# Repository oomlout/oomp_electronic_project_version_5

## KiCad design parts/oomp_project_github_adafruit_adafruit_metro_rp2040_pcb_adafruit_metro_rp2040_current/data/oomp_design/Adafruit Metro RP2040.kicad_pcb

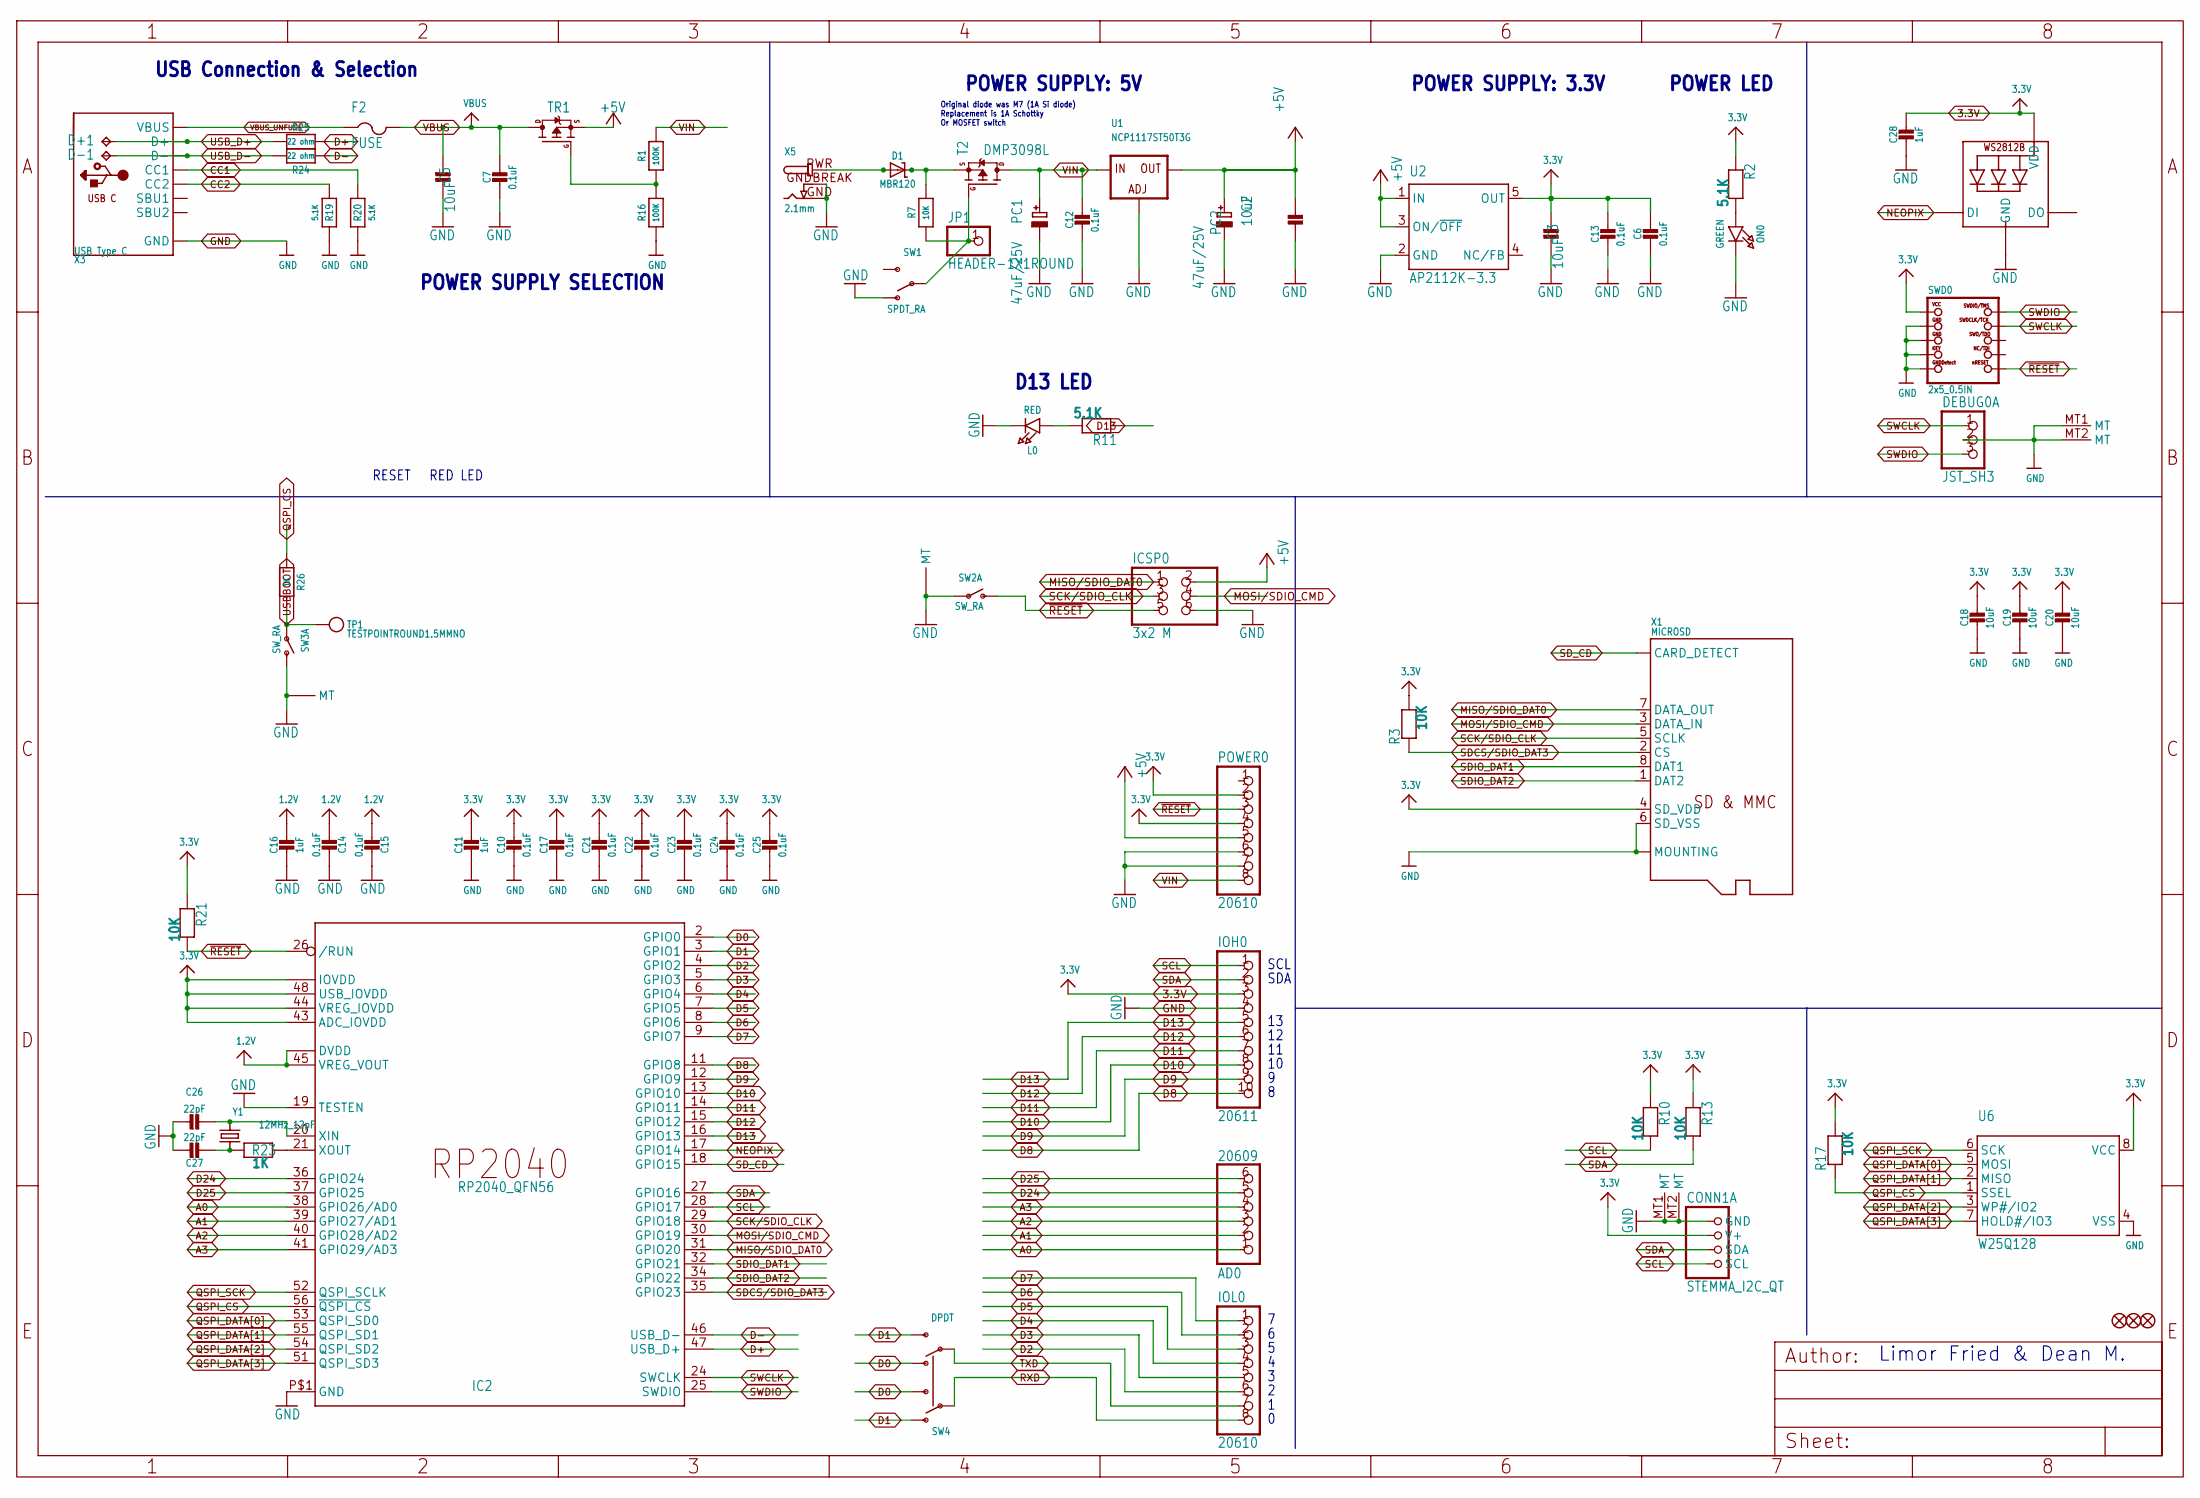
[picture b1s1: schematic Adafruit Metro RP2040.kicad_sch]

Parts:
AD0: 20609; 1X06_OVALWAVE
C2, C3, C5, C18, C19, C20: 10uF; 0805-NO
C6, C7, C10, C12, C13, C14, C15, C17, C21, C22, C23, C24, C25: 0.1uF; 0603-NO
C11, C16, C28: 1uF; 0603-NO
C26, C27: 22pF; 0603-NO
CONN1: STEMMA_I2C_QT; JST_SH4; LCSC C2845363
D1: MBR120; SOD-123
D+1: TPB1,27; B1,27
D-1: TPB1,27; B1,27
DEBUG0: JST_SH3
F2: FUSE; R1206
FD1, FD2, FD3: FIDUCIAL_1MM
IC2: RP2040_QFN56; QFN56_7MM_REDUCEDEPAD; LCSC C2040
ICSP0: 3x2 M; 2X03_ROUND_70MIL
IOH0: 20611; 1X10_OVALWAVE
IOL0: 20610; 1X08_OVALWAVE
JP1: HEADER-1X1ROUND; 1X01_ROUND
L0: RED; CHIPLED_0603_NOOUTLINE
LED2: WS2812B_3535FULL; LED3535_FULLPADS
ON0: GREEN; CHIPLED_0603_NOOUTLINE
PC1, PC2: 47uF/25V; PANASONIC_D
POWER0: 20610; 1X08_OVALWAVE
R1, R16: 100K; 0603-NO
R2, R11, R19, R20: 5.1K; 0603-NO
R3, R7, R10, R13, R17, R21: 10K; 0603-NO
R23, R26: 1K; 0603-NO
R24, R25: 22 ohm; 0603-NO
SW1: SPDT_RA; SPDT_SMT_SSSS811101
SW2, SW3: SW_RA; SPST_TACTILE_RA; LCSC C778159
SW4: DPDT; EG1390; LCSC C2837066
SWD0: 2x5_0.5IN; 2X05_1.27MM_BOX_POSTS
T2: DMP3098L; SOT23-WIDE
TP1: TESTPOINTROUND1.5MMNO; TESTPOINT_ROUND_1.5MM_NO
TR1: DMP3098L; SOT23-WIDE
U1: NCP1117ST50T3G; SOT223-R
U2: AP2112K-3.3; SOT23-DBV
U6: W25Q128; SOIC8_208MIL
X1: MICROSD; JLC_ROTATION 90
X3: USB Type C; USB_C_CUSB31-CFM2AX-01-X; LCSC C165948
X5: 2.1mm; DCJACK_2MM_PTH
Y1: 12MHz_12pF; CRYSTAL_2.5X2

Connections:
1.2V: C14.2, C15.2, C16.1, IC2.23 (DVDD), IC2.45 (VREG_VOUT), IC2.50 (DVDD)
3.3V: C3.2, C6.2, C10.1, C11.1, C13.1, C17.1, C18.1, C19.1, C20.1, C21.1, C22.1, C23.1, C24.1, C25.1, C28.1, CONN1.2 (V+), IC2.1 (IOVDD), IC2.10 (IOVDD), IC2.22 (IOVDD), IC2.33 (IOVDD), IC2.42 (IOVDD), IC2.43 (ADC_IOVDD), IC2.44 (VREG_IOVDD), IC2.48 (USB_IOVDD), IC2.49 (IOVDD), IOH0.3, LED2.2 (VDD), POWER0.2, POWER0.4, R2.1, R3.2, R10.1, R13.1, R17.2, R21.1, SWD0.1 (VCC), U2.5 (OUT), U6.8 (VCC), X1.4 (SD_VDD)
+5V: C2.2, ICSP0.2, PC2.+, POWER0.5, TR1.2 (S), U1.2 (OUT), U1.4 (OUT), U2.1 (IN), U2.3 (ON/~OFF)
A0: AD0.1, IC2.38 (GPIO26/AD0)
A1: AD0.2, IC2.39 (GPIO27/AD1)
A2: AD0.3, IC2.40 (GPIO28/AD2)
A3: AD0.4, IC2.41 (GPIO29/AD3)
CC1: R20.2, X3.A5 (CC1)
CC2: R19.2, X3.B5 (CC2)
D0: IC2.2 (GPIO0), SW4.O2, SW4.S1
D1: IC2.3 (GPIO1), SW4.O1, SW4.S2
D2: IC2.4 (GPIO2), IOL0.6
D3: IC2.5 (GPIO3), IOL0.5
D4: IC2.6 (GPIO4), IOL0.4
D5: IC2.7 (GPIO5), IOL0.3
D6: IC2.8 (GPIO6), IOL0.2
D7: IC2.9 (GPIO7), IOL0.1
D8: IC2.11 (GPIO8), IOH0.10
D9: IC2.12 (GPIO9), IOH0.9
D10: IC2.13 (GPIO10), IOH0.8
D11: IC2.14 (GPIO11), IOH0.7
D12: IC2.15 (GPIO12), IOH0.6
D13: IC2.16 (GPIO13), IOH0.5, R11.1
D24: AD0.5, IC2.36 (GPIO24)
D25: AD0.6, IC2.37 (GPIO25)
D+: IC2.47 (USB_D+), R25.2
D-: IC2.46 (USB_D-), R24.2
GND: C2.1, C3.1, C5.1, C6.1, C7.2, C10.2, C11.2, C12.2, C13.2, C14.1, C15.1, C16.2, C17.2, C18.2, C19.2, C20.2, C21.2, C22.2, C23.2, C24.2, C25.2, C26.1, C27.1, C28.2, CONN1.1 (GND), CONN1.MT1 (MT), CONN1.MT2 (MT), DEBUG0.2, DEBUG0.MT1 (MT), DEBUG0.MT2 (MT), IC2.19 (TESTEN), IC2.P$1 (GND), ICSP0.6, IOH0.4, L0.C, LED2.4 (GND), ON0.C, PC1.-, PC2.-, POWER0.6, POWER0.7, R16.1, R19.1, R20.1, SW1.A (O), SW2.1, SW2.MT1 (MT), SW2.MT2 (MT), SW3.2 (S), SW3.MT1 (MT), SW3.MT2 (MT), SWD0.3 (GND), SWD0.5 (GND), SWD0.7 (KEY), SWD0.9 (GNDDETECT), U1.1 (ADJ), U2.2 (GND), U6.4 (VSS), X1.6 (SD_VSS), X1.MT1 (MOUNTING), X1.MT2 (MOUNTING), X3.A1B12 (GND), X3.B1A12 (GND), X5.GND, X5.GNDBREAK
MISO/SDIO_DAT0: IC2.31 (GPIO20), ICSP0.1, X1.7 (DATA_OUT)
MOSI/SDIO_CMD: IC2.30 (GPIO19), ICSP0.4, X1.3 (DATA_IN)
unnamed: L0.A, R11.2
unnamed: ON0.A, R2.2
unnamed: C26.2, IC2.20 (XIN), Y1.3 (2)
unnamed: C27.2, R23.1, Y1.1
unnamed: R1.1, R16.2, TR1.1 (G)
unnamed: IC2.21 (XOUT), R23.2
unnamed: D1.C, R7.2, T2.2 (S)
NEOPIX: IC2.17 (GPIO14), LED2.1 (DI)
PWRIN: D1.A, X5.PWR
PWR_SWITCH: JP1.1, R7.1, SW1.B, T2.1 (G)
QSPI_CS: IC2.56 (~QSPI_CS), R17.1, R26.1, U6.1 (SSEL)
QSPI_DATA[0]: IC2.53 (QSPI_SD0), U6.5 (MOSI)
QSPI_DATA[1]: IC2.55 (QSPI_SD1), U6.2 (MISO)
QSPI_DATA[2]: IC2.54 (QSPI_SD2), U6.3 (WP#/IO2)
QSPI_DATA[3]: IC2.51 (QSPI_SD3), U6.7 (HOLD#/IO3)
QSPI_SCK: IC2.52 (QSPI_SCLK), U6.6 (SCK)
RXD: IOL0.8, SW4.P1
SCK/SDIO_CLK: IC2.29 (GPIO18), ICSP0.3, X1.5 (SCLK)
SCL: CONN1.4 (SCL), IC2.28 (GPIO17), IOH0.1, R10.2
SDA: CONN1.3 (SDA), IC2.27 (GPIO16), IOH0.2, R13.2
SDCS/SDIO_DAT3: IC2.35 (GPIO23), R3.1, X1.2 (CS)
SDIO_DAT1: IC2.32 (GPIO21), X1.8 (DAT1)
SDIO_DAT2: IC2.34 (GPIO22), X1.1 (DAT2)
SD_CD: IC2.18 (GPIO15), X1.CD1 (CARD_DETECT), X1.CD2 (CARD_DETECT)
SWCLK: DEBUG0.1, IC2.24 (SWCLK), SWD0.4 (SWDCLK)
SWDIO: DEBUG0.3, IC2.25 (SWDIO), SWD0.2 (SWDIO)
TXD: IOL0.7, SW4.P2
USBBOOT: R26.2, SW3.1, TP1.P$1
USB_D+: D+1.TP, R25.1, X3.A6 (D+), X3.B6 (D+)
USB_D-: D-1.TP, R24.1, X3.A7 (D-), X3.B7 (D-)
VBUS: C5.2, C7.1, F2.2, TR1.3 (D)
VBUS_UNFUSE: F2.1, X3.A4B9 (VBUS), X3.B4A9 (VBUS)
VIN: C12.1, PC1.+, POWER0.8, R1.2, T2.3 (D), U1.3 (IN)
~RESET: IC2.26 (/RUN), ICSP0.5, POWER0.3, R21.2, SW2.2 (S), SWD0.10 (NRESET)

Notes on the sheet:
D13 LED
RESET
SCL
SDA
POWER LED
POWER SUPPLY: 5V
Limor Fried & Dean M.
POWER SUPPLY: 3.3V
POWER SUPPLY SELECTION
USB Connection & Selection
RED LED
Original diode was M7 (1A Si diode) Replacement is 1A Schottky Or MOSFET switch

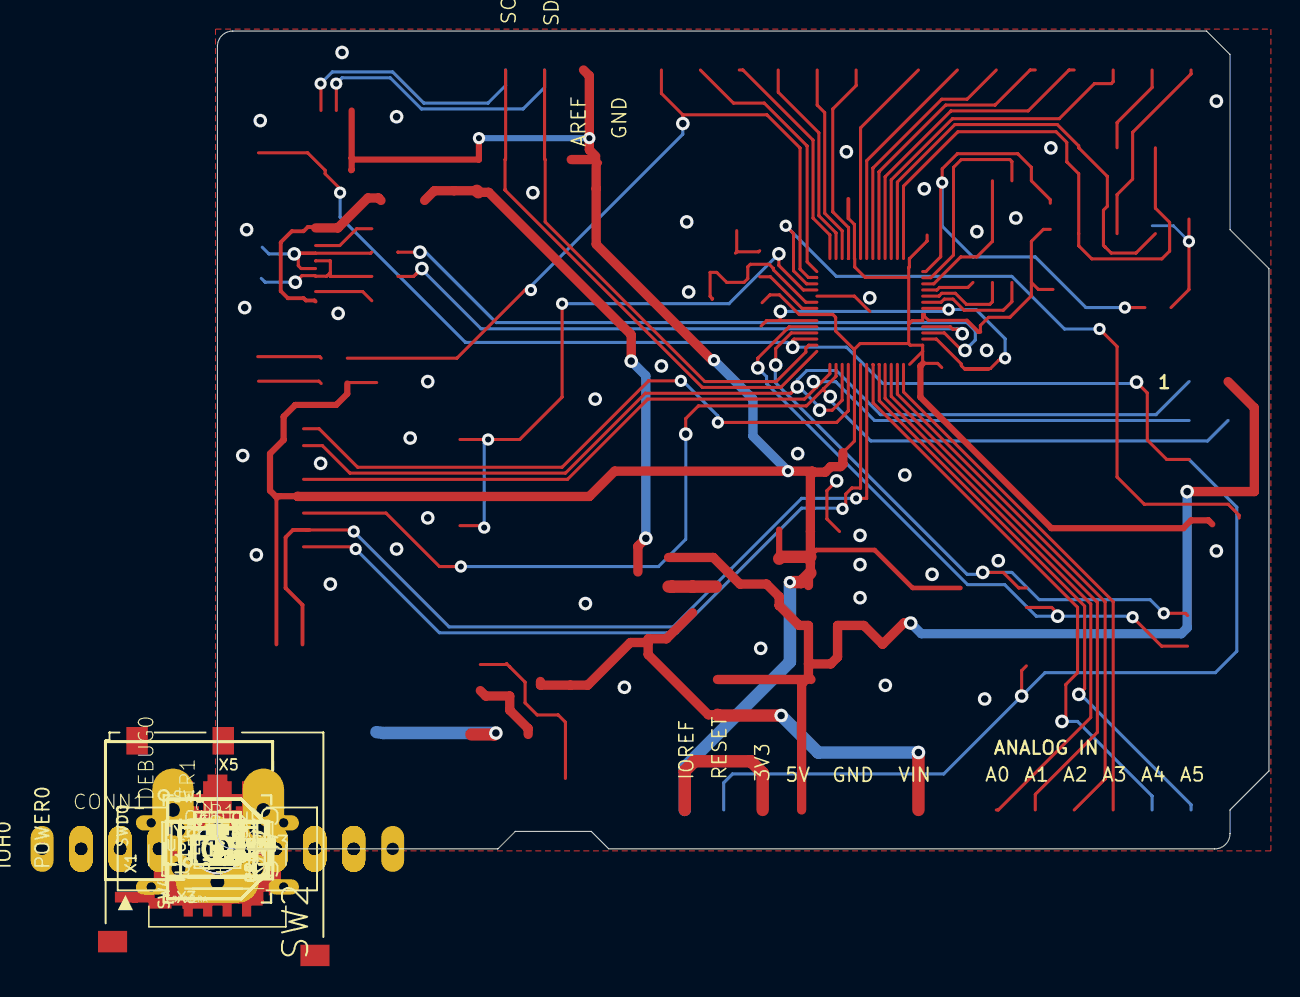
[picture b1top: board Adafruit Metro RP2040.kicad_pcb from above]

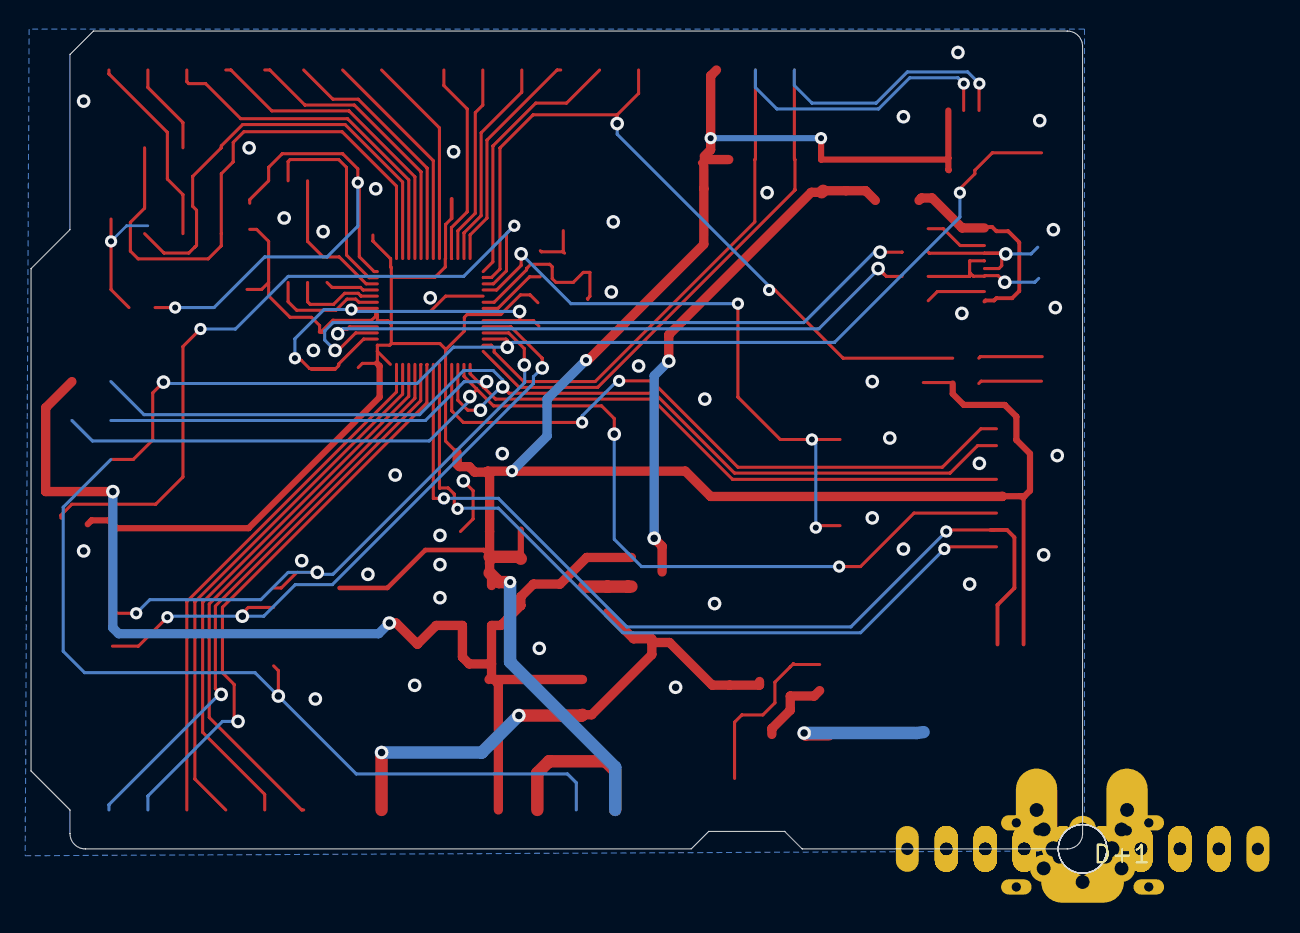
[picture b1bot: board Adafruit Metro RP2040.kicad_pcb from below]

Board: 2 copper layers, 68.6 x 53.3 mm, 83 parts (4 on the bottom side), 64 nets.

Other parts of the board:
U$11: PCBFEAT-REV-040
U$15: METRO_RP2040_BOT
U$29: METRO_RP2040_TOP
UNK_HOLE_0: dummyfp0
UNK_HOLE_1: dummyfp1
UNK_HOLE_2: dummyfp2
UNK_HOLE_3: dummyfp3

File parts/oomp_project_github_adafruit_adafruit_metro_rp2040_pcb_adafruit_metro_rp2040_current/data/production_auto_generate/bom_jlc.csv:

Comment,Designator,Footprint,LCSC Part #
,JP1,Adafruit Metro RP2040-import-fps:1X01_ROUND,C7501259
,U$15,Adafruit Metro RP2040-import-fps:METRO_RP2040_BOT,
,U$29,Adafruit Metro RP2040-import-fps:METRO_RP2040_TOP,
,U$11,Adafruit Metro RP2040-import-fps:PCBFEAT-REV-040,
,TP1,Adafruit Metro RP2040-import-fps:TESTPOINT_ROUND_1.5MM_NO,
0.1uF,"C6,C7,C10,C12,C13,C14,C15,C17,C21,C22,C23,C24,C25",Adafruit Metro RP2040-import-fps:0603-NO,C14663
100K,"R1,R16",Adafruit Metro RP2040-import-fps:0603-NO,C25803
10K,"R3,R7,R10,R13,R17,R21",Adafruit Metro RP2040-import-fps:0603-NO,C98220
10uF,"C2,C3,C5,C18,C19,C20",Adafruit Metro RP2040-import-fps:0805-NO,
12MHz_12pF,Y1,Adafruit Metro RP2040-import-fps:CRYSTAL_2.5X2,
1K,"R23,R26",Adafruit Metro RP2040-import-fps:0603-NO,C2907002
1uF,"C11,C16,C28",Adafruit Metro RP2040-import-fps:0603-NO,C5673
2.1mm,X5,Adafruit Metro RP2040-import-fps:DCJACK_2MM_PTH,
20609,AD0,Adafruit Metro RP2040-import-fps:1X06_OVALWAVE,C37208
20610,"IOL0,POWER0",Adafruit Metro RP2040-import-fps:1X08_OVALWAVE,C492421
20611,IOH0,Adafruit Metro RP2040-import-fps:1X10_OVALWAVE,C57369
22 ohm,"R24,R25",Adafruit Metro RP2040-import-fps:0603-NO,C23345
22pF,"C26,C27",Adafruit Metro RP2040-import-fps:0603-NO,C105620
2x5_0.5IN,SWD0,Adafruit Metro RP2040-import-fps:2X05_1.27MM_BOX_POSTS,
3x2 M,ICSP0,Adafruit Metro RP2040-import-fps:2X03_ROUND_70MIL,
47uF/25V,"PC1,PC2",Adafruit Metro RP2040-import-fps:PANASONIC_D,
5.1K,"R2,R11,R19,R20",Adafruit Metro RP2040-import-fps:0603-NO,C23186
AP2112K-3.3,U2,Adafruit Metro RP2040-import-fps:SOT23-DBV,
DMP3098L,"T2,TR1",Adafruit Metro RP2040-import-fps:SOT23-WIDE,
DPDT,SW4,Adafruit Metro RP2040-import-fps:EG1390,
FIDUCIAL_1MM,"FD1,FD2,FD3",Adafruit Metro RP2040-import-fps:FIDUCIAL_1MM,
FUSE,F2,Adafruit Metro RP2040-import-fps:R1206,
GREEN,ON0,Adafruit Metro RP2040-import-fps:CHIPLED_0603_NOOUTLINE,
JST_SH3,DEBUG0,Adafruit Metro RP2040-import-fps:JST_SH3,
MBR120,D1,Adafruit Metro RP2040-import-fps:SOD-123,
MICROSD,X1,Adafruit Metro RP2040-import-fps:MICROSD,
NCP1117ST50T3G,U1,Adafruit Metro RP2040-import-fps:SOT223-R,
RED,L0,Adafruit Metro RP2040-import-fps:CHIPLED_0603_NOOUTLINE,
RP2040_QFN56,IC2,Adafruit Metro RP2040-import-fps:QFN56_7MM_REDUCEDEPAD,
SPDT_RA,SW1,Adafruit Metro RP2040-import-fps:SPDT_SMT_SSSS811101,
STEMMA_I2C_QT,CONN1,Adafruit Metro RP2040-import-fps:JST_SH4,C160404
SW_RA,"SW2,SW3",Adafruit Metro RP2040-import-fps:SPST_TACTILE_RA,
"TPB1,27","D+1,D-1","Adafruit Metro RP2040-import-fps:B1,27",
USB Type C,X3,Adafruit Metro RP2040-import-fps:USB_C_CUSB31-CFM2AX-01-X,
W25Q128,U6,Adafruit Metro RP2040-import-fps:SOIC8_208MIL,
WS2812B_3535FULL,LED2,Adafruit Metro RP2040-import-fps:LED3535_FULLPADS,

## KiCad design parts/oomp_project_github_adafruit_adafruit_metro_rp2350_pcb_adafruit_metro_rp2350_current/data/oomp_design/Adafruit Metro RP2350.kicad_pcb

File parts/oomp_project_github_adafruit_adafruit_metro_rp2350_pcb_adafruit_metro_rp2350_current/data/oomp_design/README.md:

# OOMP KiCad design copy

Open `Adafruit Metro RP2350.kicad_pro` (or the `.kicad_pcb` / `.kicad_sch`) in KiCad. Local OOMP libraries are under `libraries/`. Original inputs are preserved in [../original/](../original/).

Only verified unchanged installed KiCad defaults were renamed. Modified, custom, unmatched and unavailable items remain unchanged. Soldering variants are never swapped during conversion. Existing pad coordinates, nets and UUIDs are preserved.

See [conversion_report.yaml](conversion_report.yaml) for every conversion and skip. Copy this directory before editing; regeneration refuses to overwrite edited design files.

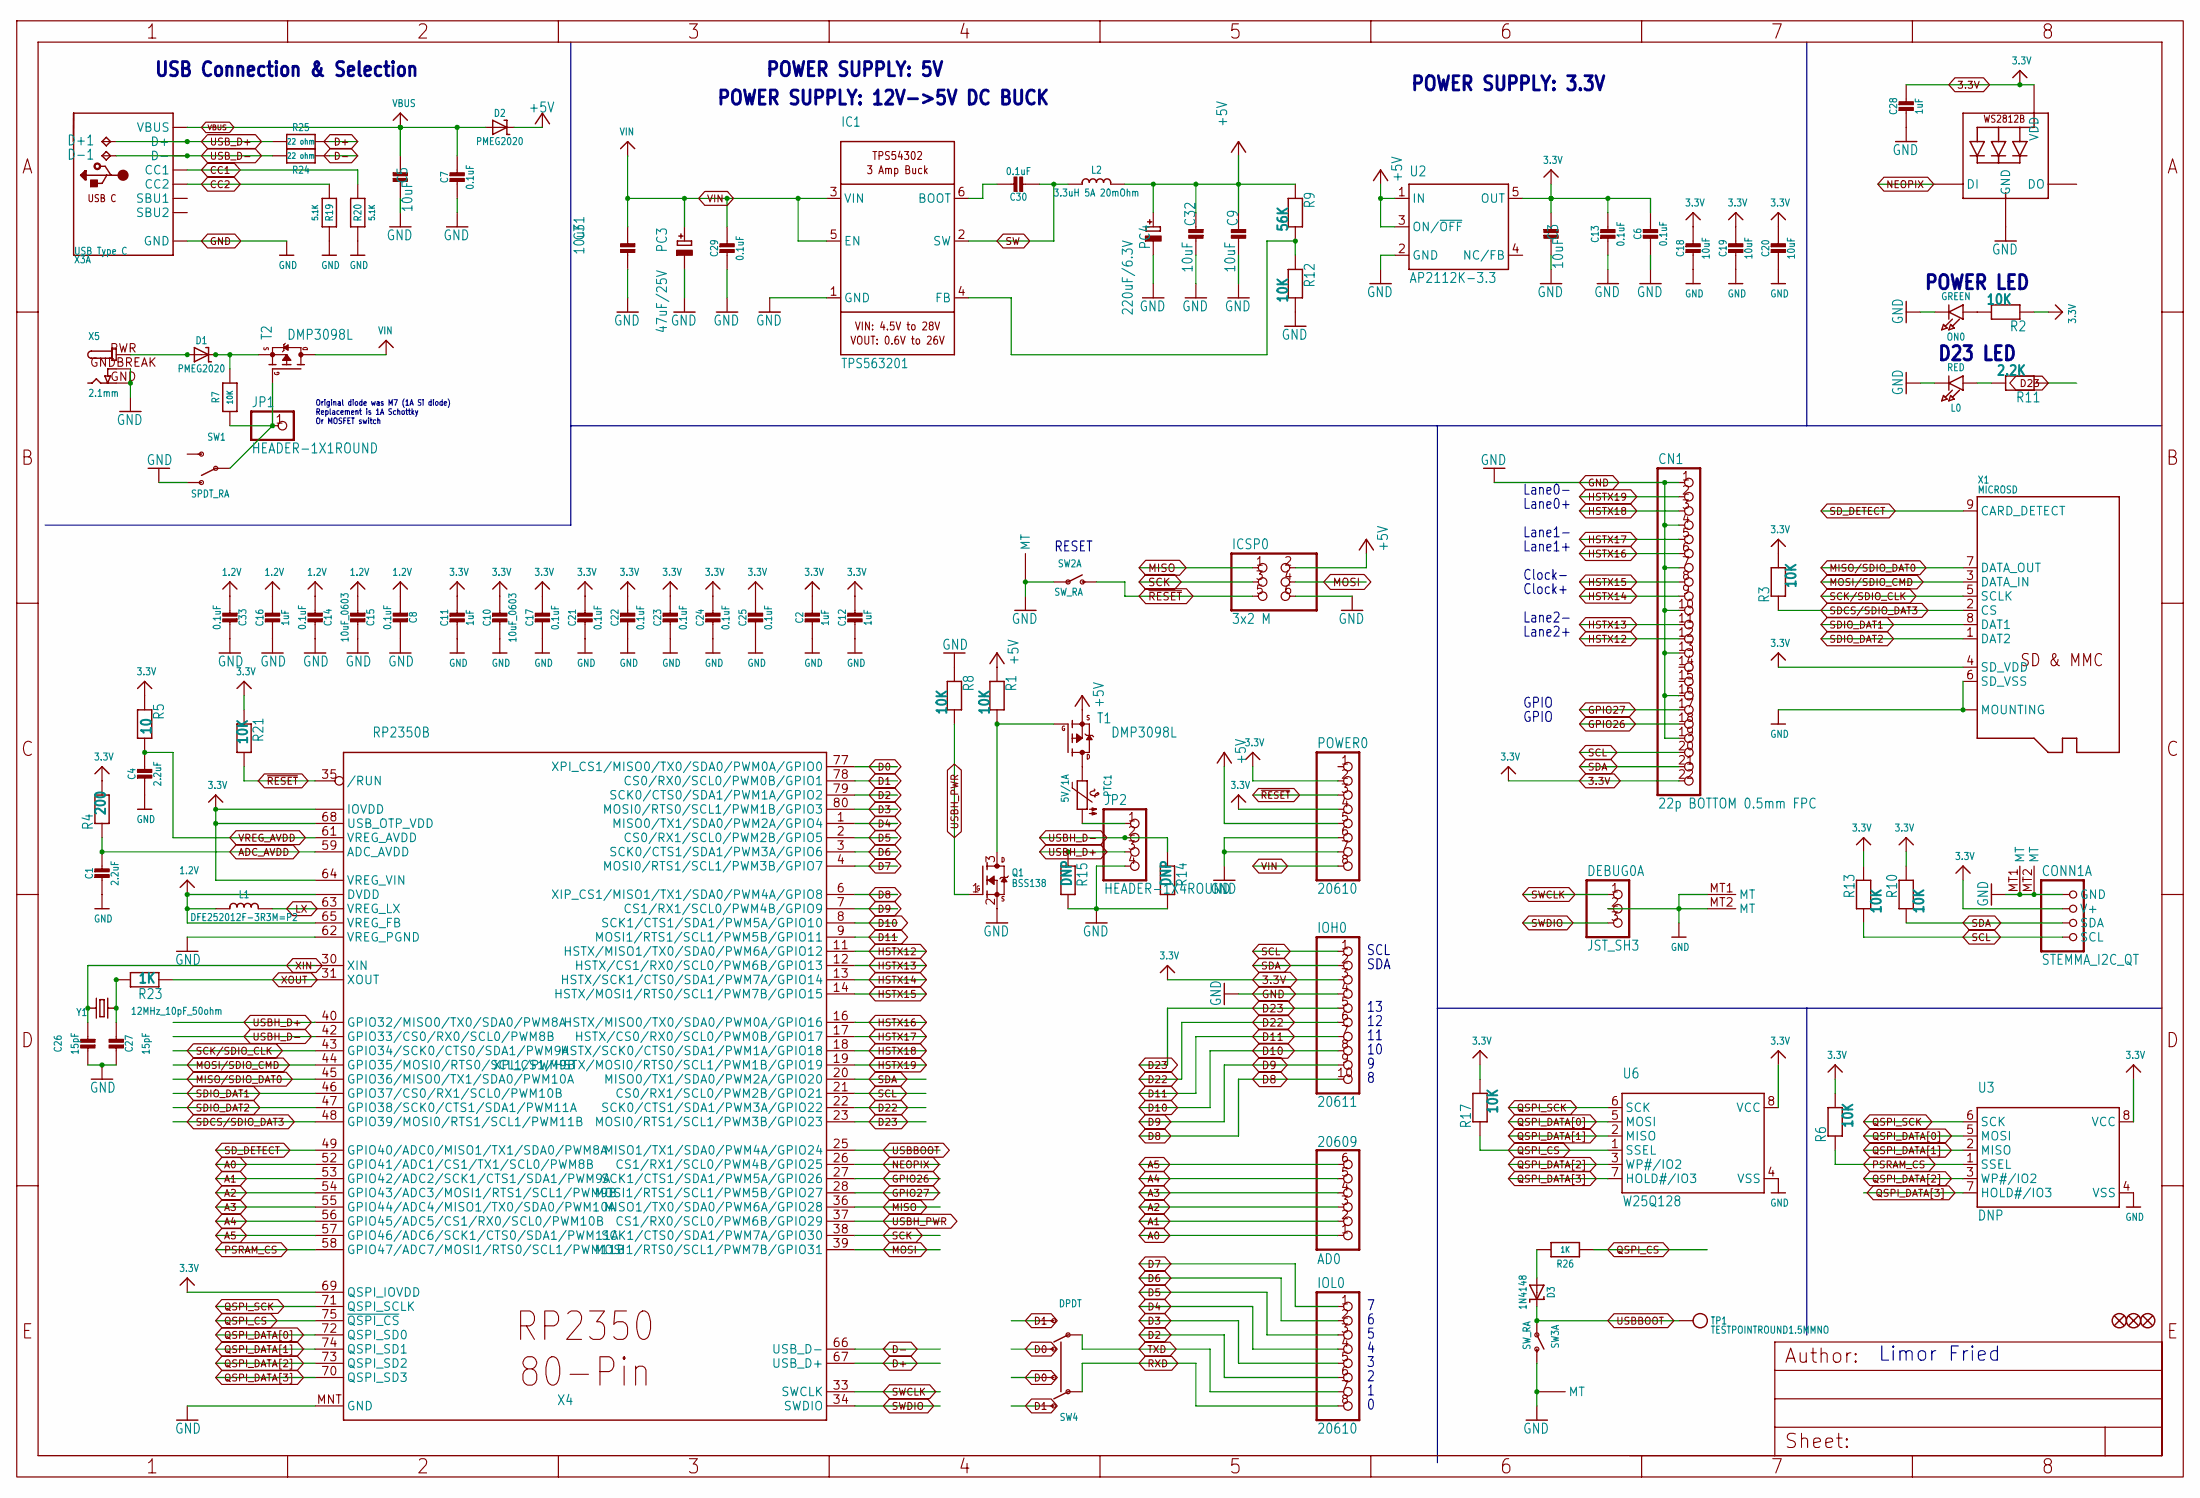
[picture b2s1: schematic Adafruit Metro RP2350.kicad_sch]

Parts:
AD0: 20609; 1X06_OVALWAVE
C1, C4: 2.2uF; 0603-NO
C2, C11, C12, C16, C28: 1uF; 0603-NO
C3, C5, C9, C18, C19, C20, C31, C32: 10uF; 0805-NO
C6, C7, C8, C13, C14, C17, C21, C22, C23, C24, C25, C29, C30, C33: 0.1uF; 0603-NO
C10, C15: 10uF_0603; 0603-NO_WIDE
C26, C27: 15pF; 0603-NO
CN1: 22p BOTTOM 0.5mm FPC; FPC_22PIN
CONN1: STEMMA_I2C_QT; JST_SH4; LCSC C2845363
D1, D2: PMEG2020; SOD-323
D3: 1N4148; SOD-323
D+1: TPB1,27; B1,27
D-1: TPB1,27; B1,27
DEBUG0: JST_SH3; JST_SH3_RA
FD1, FD2, FD3: FIDUCIAL_1MM
IC1: TPS563201; SOT23-6
ICSP0: 3x2 M; 2X03_ROUND_70MIL
IOH0: 20611; 1X10_OVALWAVE
IOL0: 20610; 1X08_OVALWAVE
JP1: HEADER-1X1ROUND; 1X01_ROUND
JP2: HEADER-1X4ROUND; 1X04_ROUND
L0: RED; CHIPLED_0603_NOOUTLINE
L1: DFE252012F-3R3M=P2; INDUCTOR_1007
L2: 3.3uH 5A 20mOhm; INDUCTOR_0603S
LED2: WS2812B_3535FULL; LED3535_FULLPADS
ON0: GREEN; CHIPLED_0603_NOOUTLINE
PC3: 47uF/25V; PANASONIC_D
PC4: 220uF/6.3V; PANASONIC_D
POWER0: 20610; 1X08_OVALWAVE
PTC1: 5V/1A; 0805-NO
Q1: BSS138; SOT23-WIDE
R1, R2, R3, R6, R7, R8, R10, R12, R13, R17, R21: 10K; 0603-NO
R4: 200; 0603-NO
R5: 10; 0603-NO
R9: 56K; 0603-NO
R11: 2.2K; 0603-NO
R14, R15: DNP; 0603-NO
R19, R20: 5.1K; 0603-NO
R23, R26: 1K; 0603-NO
R24, R25: 22 ohm; 0603-NO
SW1: SPDT_RA; SPDT_SMT_SSSS811101
SW2, SW3: SW_RA; SPST_TACTILE_RA; LCSC C778159
SW4: DPDT; EG1390; LCSC C2837066
T1, T2: DMP3098L; SOT23-WIDE
TP1: TESTPOINTROUND1.5MMNO; TESTPOINT_ROUND_1.5MM_NO
U2: AP2112K-3.3; SOT23-DBV
U3: DNP; SOIC8_208MIL
U6: W25Q128; SOIC8_208MIL
X1: MICROSD; MOLEX_104031-0811
X3: USB Type C; USB_C_CUSB31-CFM2AX-01-X; LCSC C165948
X4: RP2350B; QFN80
X5: 2.1mm; DCJACK_2MM_PTH
Y1: 12MHz_10pF_50ohm; CRYSTAL_2.5X2

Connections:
1.2V: C8.2, C14.2, C15.2, C16.1, C33.2, L1.P$1 (1), X4.10 (DVDD), X4.32 (DVDD), X4.51 (DVDD), X4.65 (VREG_FB)
3.3V: C2.1, C3.2, C6.2, C10.1, C11.1, C12.1, C13.1, C17.1, C18.1, C19.1, C20.1, C21.1, C22.1, C23.1, C24.1, C25.1, C28.1, CN1.22, CONN1.2 (V+), IOH0.3, LED2.2 (VDD), POWER0.2, POWER0.4, R2.1, R3.2, R4.2, R5.1, R6.2, R10.1, R13.1, R17.2, R21.1, U2.5 (OUT), U3.8 (VCC), U6.8 (VCC), X1.4 (SD_VDD), X4.5 (IOVDD), X4.15 (IOVDD), X4.24 (IOVDD), X4.29 (IOVDD), X4.41 (IOVDD), X4.50 (IOVDD), X4.60 (IOVDD), X4.64 (VREG_VIN), X4.68 (USB_OTP_VDD), X4.69 (QSPI_IOVDD), X4.76 (IOVDD)
+5V: C9.2, C32.2, D2.C, ICSP0.2, L2.P$2 (2), PC4.+, POWER0.5, R1.1, R9.1, T1.2 (S), U2.1 (IN), U2.3 (ON/~OFF)
A0: AD0.1, X4.52 (GPIO41/ADC1/CS1/TX1/SCL0/PWM8B)
A1: AD0.2, X4.53 (GPIO42/ADC2/SCK1/CTS1/SDA1/PWM9A)
A2: AD0.3, X4.54 (GPIO43/ADC3/MOSI1/RTS1/SCL1/PWM9B)
A3: AD0.4, X4.55 (GPIO44/ADC4/MISO1/TX0/SDA0/PWM10A)
A4: AD0.5, X4.56 (GPIO45/ADC5/CS1/RX0/SCL0/PWM10B)
A5: AD0.6, X4.57 (GPIO46/ADC6/SCK1/CTS0/SDA1/PWM11A)
ADC_AVDD: C1.1, R4.1, X4.59 (ADC_AVDD)
CC1: R20.2, X3.A5 (CC1)
CC2: R19.2, X3.B5 (CC2)
D0: SW4.O2, SW4.S1, X4.77 (XPI_CS1/MISO0/TX0/SDA0/PWM0A/GPIO0)
D1: SW4.O1, SW4.S2, X4.78 (CS0/RX0/SCL0/PWM0B/GPIO1)
D2: IOL0.6, X4.79 (SCK0/CTS0/SDA1/PWM1A/GPIO2)
D3: IOL0.5, X4.80 (MOSI0/RTS0/SCL1/PWM1B/GPIO3)
D4: IOL0.4, X4.1 (MISO0/TX1/SDA0/PWM2A/GPIO4)
D5: IOL0.3, X4.2 (CS0/RX1/SCL0/PWM2B/GPIO5)
D6: IOL0.2, X4.3 (SCK0/CTS1/SDA1/PWM3A/GPIO6)
D7: IOL0.1, X4.4 (MOSI0/RTS1/SCL1/PWM3B/GPIO7)
D8: IOH0.10, X4.6 (XIP_CS1/MISO1/TX1/SDA0/PWM4A/GPIO8)
D9: IOH0.9, X4.7 (CS1/RX1/SCL0/PWM4B/GPIO9)
D10: IOH0.8, X4.8 (SCK1/CTS1/SDA1/PWM5A/GPIO10)
D11: IOH0.7, X4.9 (MOSI1/RTS1/SCL1/PWM5B/GPIO11)
D22: IOH0.6, X4.22 (SCK0/CTS1/SDA1/PWM3A/GPIO22)
D23: IOH0.5, R11.1, X4.23 (MOSI0/RTS1/SCL1/PWM3B/GPIO23)
D+: R25.2, X4.67 (USB_D+)
D-: R24.2, X4.66 (USB_D-)
GND: C1.2, C2.2, C3.1, C4.2, C5.1, C6.1, C7.2, C8.1, C9.1, C10.2, C11.2, C12.2, C13.2, C14.1, C15.1, C16.2, C17.2, C18.2, C19.2, C20.2, C21.2, C22.2, C23.2, C24.2, C25.2, C26.1, C27.1, C28.2, C29.2, C31.1, C32.1, C33.1, CN1.1, CN1.4, CN1.7, CN1.10, CN1.13, CN1.16, CN1.19, CONN1.1 (GND), CONN1.MT1 (MT), CONN1.MT2 (MT), DEBUG0.2, DEBUG0.MT1 (MT), DEBUG0.MT2 (MT), IC1.1 (GND), ICSP0.6, IOH0.4, JP2.4, L0.C, LED2.4 (GND), ON0.C, PC3.-, PC4.-, POWER0.6, POWER0.7, Q1.2 (S), R8.1, R12.2, R14.1, R15.1, R19.1, R20.1, SW1.A (O), SW2.1, SW2.MT1 (MT), SW2.MT2 (MT), SW3.2 (S), SW3.MT1 (MT), SW3.MT2 (MT), U2.2 (GND), U3.4 (VSS), U6.4 (VSS), X1.6 (SD_VSS), X1.10 (MOUNTING), X1.G1 (MOUNTING), X1.G2 (MOUNTING), X1.G3 (MOUNTING), X1.G4 (MOUNTING), X3.A1B12 (GND), X3.B1A12 (GND), X4.62 (VREG_PGND), X4.MNT (GND), X5.GND, X5.GNDBREAK
GPIO26: CN1.18, X4.27 (SCK1/CTS1/SDA1/PWM5A/GPIO26)
GPIO27: CN1.17, X4.28 (MOSI1/RTS1/SCL1/PWM5B/GPIO27)
HSTX12: CN1.12, X4.11 (HSTX/MISO1/TX0/SDA0/PWM6A/GPIO12)
HSTX13: CN1.11, X4.12 (HSTX/CS1/RX0/SCL0/PWM6B/GPIO13)
HSTX14: CN1.9, X4.13 (HSTX/SCK1/CTS0/SDA1/PWM7A/GPIO14)
HSTX15: CN1.8, X4.14 (HSTX/MOSI1/RTS0/SCL1/PWM7B/GPIO15)
HSTX16: CN1.6, X4.16 (HSTX/MISO0/TX0/SDA0/PWM0A/GPIO16)
HSTX17: CN1.5, X4.17 (HSTX/CS0/RX0/SCL0/PWM0B/GPIO17)
HSTX18: CN1.3, X4.18 (HSTX/SCK0/CTS0/SDA1/PWM1A/GPIO18)
HSTX19: CN1.2, X4.19 (XPI_CS1/HSTX/MOSI0/RTS0/SCL1/PWM1B/GPIO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)
LX: L1.P$2 (2), X4.63 (VREG_LX)
MISO: ICSP0.1, X4.36 (MISO1/TX0/SDA0/PWM6A/GPIO28)
MISO/SDIO_DAT0: X1.7 (DATA_OUT), X4.45 (GPIO36/MISO0/TX1/SDA0/PWM10A)
MOSI: ICSP0.4, X4.39 (MOSI1/RTS0/SCL1/PWM7B/GPIO31)
MOSI/SDIO_CMD: X1.3 (DATA_IN), X4.44 (GPIO35/MOSI0/RTS0/SCL1/PWM9B)
unnamed: L0.A, R11.2
unnamed: ON0.A, R2.2
unnamed: JP2.1, PTC1.1
unnamed: PTC1.2, T1.3 (D)
unnamed: Q1.3 (D), R1.2, T1.1 (G)
unnamed: D3.A, R26.2
unnamed: C30.1, IC1.6 (BOOT)
unnamed: IC1.4 (FB), R9.2, R12.1
unnamed: C27.2, R23.1, Y1.3 (2)
unnamed: D1.C, R7.2, T2.2 (S)
NEOPIX: LED2.1 (DI), X4.26 (CS1/RX1/SCL0/PWM4B/GPIO25)
PSRAM_CS: R6.1, U3.1 (SSEL), X4.58 (GPIO47/ADC7/MOSI1/RTS0/SCL1/PWM11B)
PWRIN: D1.A, X5.PWR
PWR_SWITCH: JP1.1, R7.1, SW1.B, T2.1 (G)
QSPI_CS: R17.1, R26.1, U6.1 (SSEL), X4.75 (~QSPI_CS)
QSPI_DATA[0]: U3.5 (MOSI), U6.5 (MOSI), X4.72 (QSPI_SD0)
QSPI_DATA[1]: U3.2 (MISO), U6.2 (MISO), X4.74 (QSPI_SD1)
QSPI_DATA[2]: U3.3 (WP#/IO2), U6.3 (WP#/IO2), X4.73 (QSPI_SD2)
QSPI_DATA[3]: U3.7 (HOLD#/IO3), U6.7 (HOLD#/IO3), X4.70 (QSPI_SD3)
QSPI_SCK: U3.6 (SCK), U6.6 (SCK), X4.71 (QSPI_SCLK)
RXD: IOL0.8, SW4.P1
SCK: ICSP0.3, X4.38 (SCK1/CTS0/SDA1/PWM7A/GPIO30)
SCK/SDIO_CLK: X1.5 (SCLK), X4.43 (GPIO34/SCK0/CTS0/SDA1/PWM9A)
SCL: CN1.20, CONN1.4 (SCL), IOH0.1, R13.2, X4.21 (CS0/RX1/SCL0/PWM2B/GPIO21)
SDA: CN1.21, CONN1.3 (SDA), IOH0.2, R10.2, X4.20 (MISO0/TX1/SDA0/PWM2A/GPIO20)
SDCS/SDIO_DAT3: R3.1, X1.2 (CS), X4.48 (GPIO39/MOSI0/RTS1/SCL1/PWM11B)
SDIO_DAT1: X1.8 (DAT1), X4.46 (GPIO37/CS0/RX1/SCL0/PWM10B)
SDIO_DAT2: X1.1 (DAT2), X4.47 (GPIO38/SCK0/CTS1/SDA1/PWM11A)
SD_DETECT: X1.9 (CARD_DETECT), X4.49 (GPIO40/ADC0/MISO1/TX1/SDA0/PWM8A)
SW: C30.2, IC1.2 (SW), L2.P$1 (1)
SWCLK: DEBUG0.1, X4.33 (SWCLK)
SWDIO: DEBUG0.3, X4.34 (SWDIO)
TXD: IOL0.7, SW4.P2
USBBOOT: D3.C, SW3.1, TP1.P$1, X4.25 (MISO1/TX1/SDA0/PWM4A/GPIO24)
USBH_D+: JP2.3, R15.2, X4.40 (GPIO32/MISO0/TX0/SDA0/PWM8A)
USBH_D-: JP2.2, R14.2, X4.42 (GPIO33/CS0/RX0/SCL0/PWM8B)
USBH_PWR: Q1.1 (G), R8.2, X4.37 (CS1/RX0/SCL0/PWM6B/GPIO29)
USB_D+: D+1.TP, R25.1, X3.A6 (D+), X3.B6 (D+)
USB_D-: D-1.TP, R24.1, X3.A7 (D-), X3.B7 (D-)
VBUS: C5.2, C7.1, D2.A, X3.A4B9 (VBUS), X3.B4A9 (VBUS)
VIN: C29.1, C31.2, IC1.3 (VIN), IC1.5 (EN), PC3.+, POWER0.8, T2.3 (D)
VREG_AVDD: C4.1, R5.2, X4.61 (VREG_AVDD)
XIN: C26.2, X4.30 (XIN), Y1.1
XOUT: R23.2, X4.31 (XOUT)
~RESET: ICSP0.5, POWER0.3, R21.2, SW2.2 (S), X4.35 (/RUN)

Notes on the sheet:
SCL
Clock+
Lane0+
D23 LED
POWER SUPPLY: 12V->5V DC BUCK
Lane1-
Lane2+
POWER LED
GPIO
USB Connection & Selection
POWER SUPPLY: 5V
Limor Fried
Clock-
Original diode was M7 (1A Si diode) Replacement is 1A Schottky Or MOSFET switch
POWER SUPPLY: 3.3V
Lane2-
RESET
Lane0-
SDA
Lane1+
